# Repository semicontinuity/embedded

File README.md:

Embedded projects.
================================================================================

Projects for AVR microcontrollers.
--------------------------------------------------------------------------------
- [Primitive alarm](../../tree/master/target/alarm-a)
- [Primitive terminal](../../tree/master/target/display)
- [Voltage relay](../../tree/master/target/voltage-relay)
- [Mood lamp - firmware under development](../../tree/master/target/mood-lamp)
- [Primitive motion sensor controller, that works in pair with primitive alarm](../../tree/master/target/motion-sensor-controller/firmware/main)
- [Servo controller - unfinished, no firmware yet](../../tree/master/target/motor-controller/hardware)
- [LED dimmer, controlled via CAN bus](../../tree/master/target/plc-3u-a/firmware/network-led-dimmer)
- [CAN bus router - firmware under development](../../tree/master/target/plc-6u-a/firmware/can_router)
- [Roller shutter controller, controlled via CAN bus](../../tree/master/target/roller-shutter-controller/firmware/main)
- [Humidity meter](../../tree/master/target/plc-3u-b/firmware/humidity-meter)

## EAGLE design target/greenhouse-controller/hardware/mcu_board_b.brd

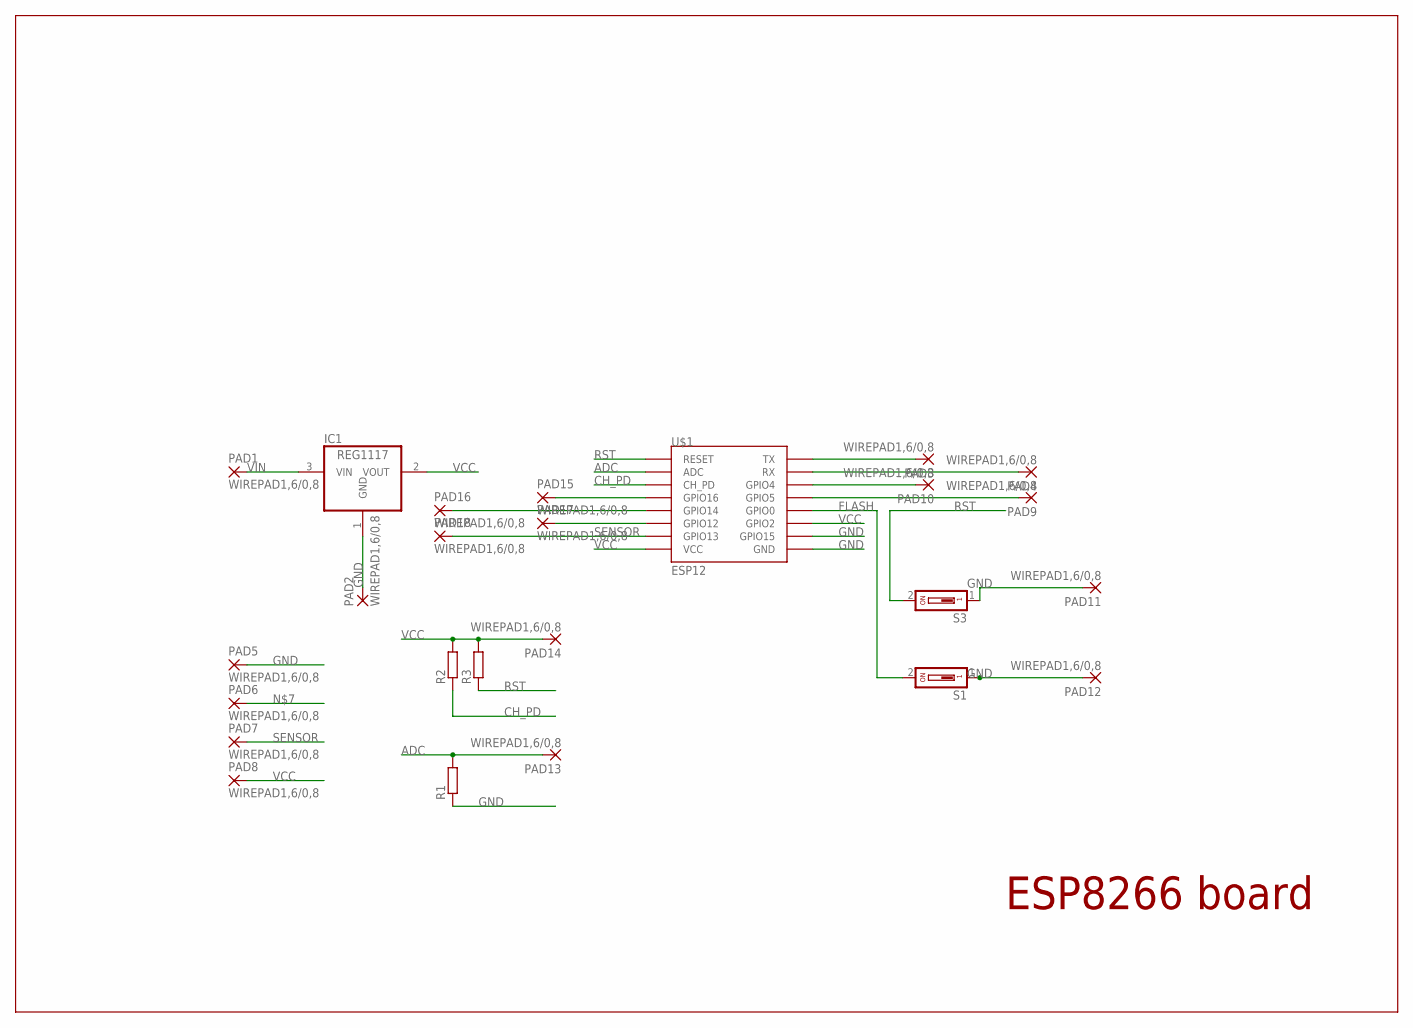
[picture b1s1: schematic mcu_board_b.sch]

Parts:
IC1: REG1117; SOT223
PAD1, PAD2, PAD3, PAD4, PAD5, PAD6, PAD7, PAD8, PAD9, PAD10, PAD11, PAD12, PAD13, PAD14, PAD15, PAD16, PAD17, PAD18: WIREPAD1,6/0,8; 1,6/0,8
R1, R2, R3: R-EU_M0805; M0805
S1, S3: DS01; DS-01
U$1: ESP12

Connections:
ADC: PAD13.1, R1.2, U$1.ADC
CH_PD: R2.1, U$1.CH_PD
FLASH: S1.2, U$1.GPIO0
GND: IC1.1 (GND), PAD2.1, PAD5.1, PAD11.1, PAD12.1, R1.1, S1.1, S3.1, U$1.GND, U$1.GPIO15
unnamed: PAD3.1, U$1.TX
unnamed: PAD4.1, U$1.RX
unnamed: PAD10.1, U$1.GPIO4
unnamed: PAD9.1, U$1.GPIO5
unnamed: PAD15.1, U$1.GPIO16
unnamed: PAD16.1, U$1.GPIO14
unnamed: PAD17.1, U$1.GPIO12
RST: R3.1, S3.2, U$1.RESET
SENSOR: PAD7.1, PAD18.1, U$1.GPIO13
VCC: IC1.2 (VOUT), PAD8.1, PAD14.1, R2.2, R3.2, U$1.GPIO2, U$1.VCC
VIN: IC1.3 (VIN), PAD1.1

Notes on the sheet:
ESP8266 board

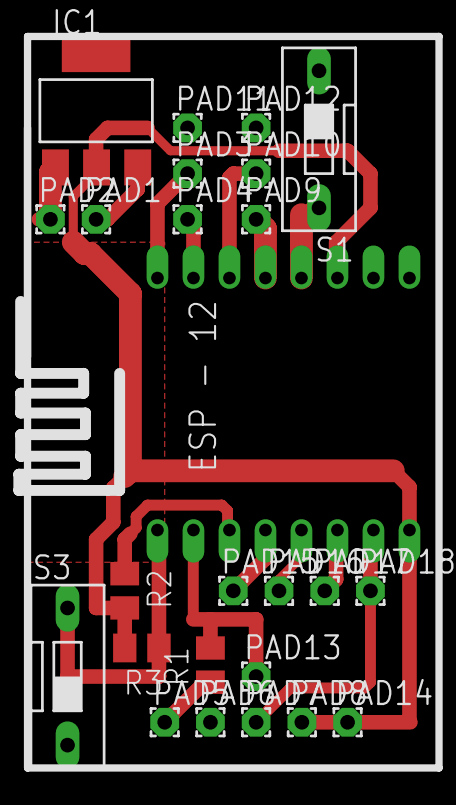
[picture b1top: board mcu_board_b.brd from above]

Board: 2 copper layers, 25 parts (0 on the bottom side), 15 nets.

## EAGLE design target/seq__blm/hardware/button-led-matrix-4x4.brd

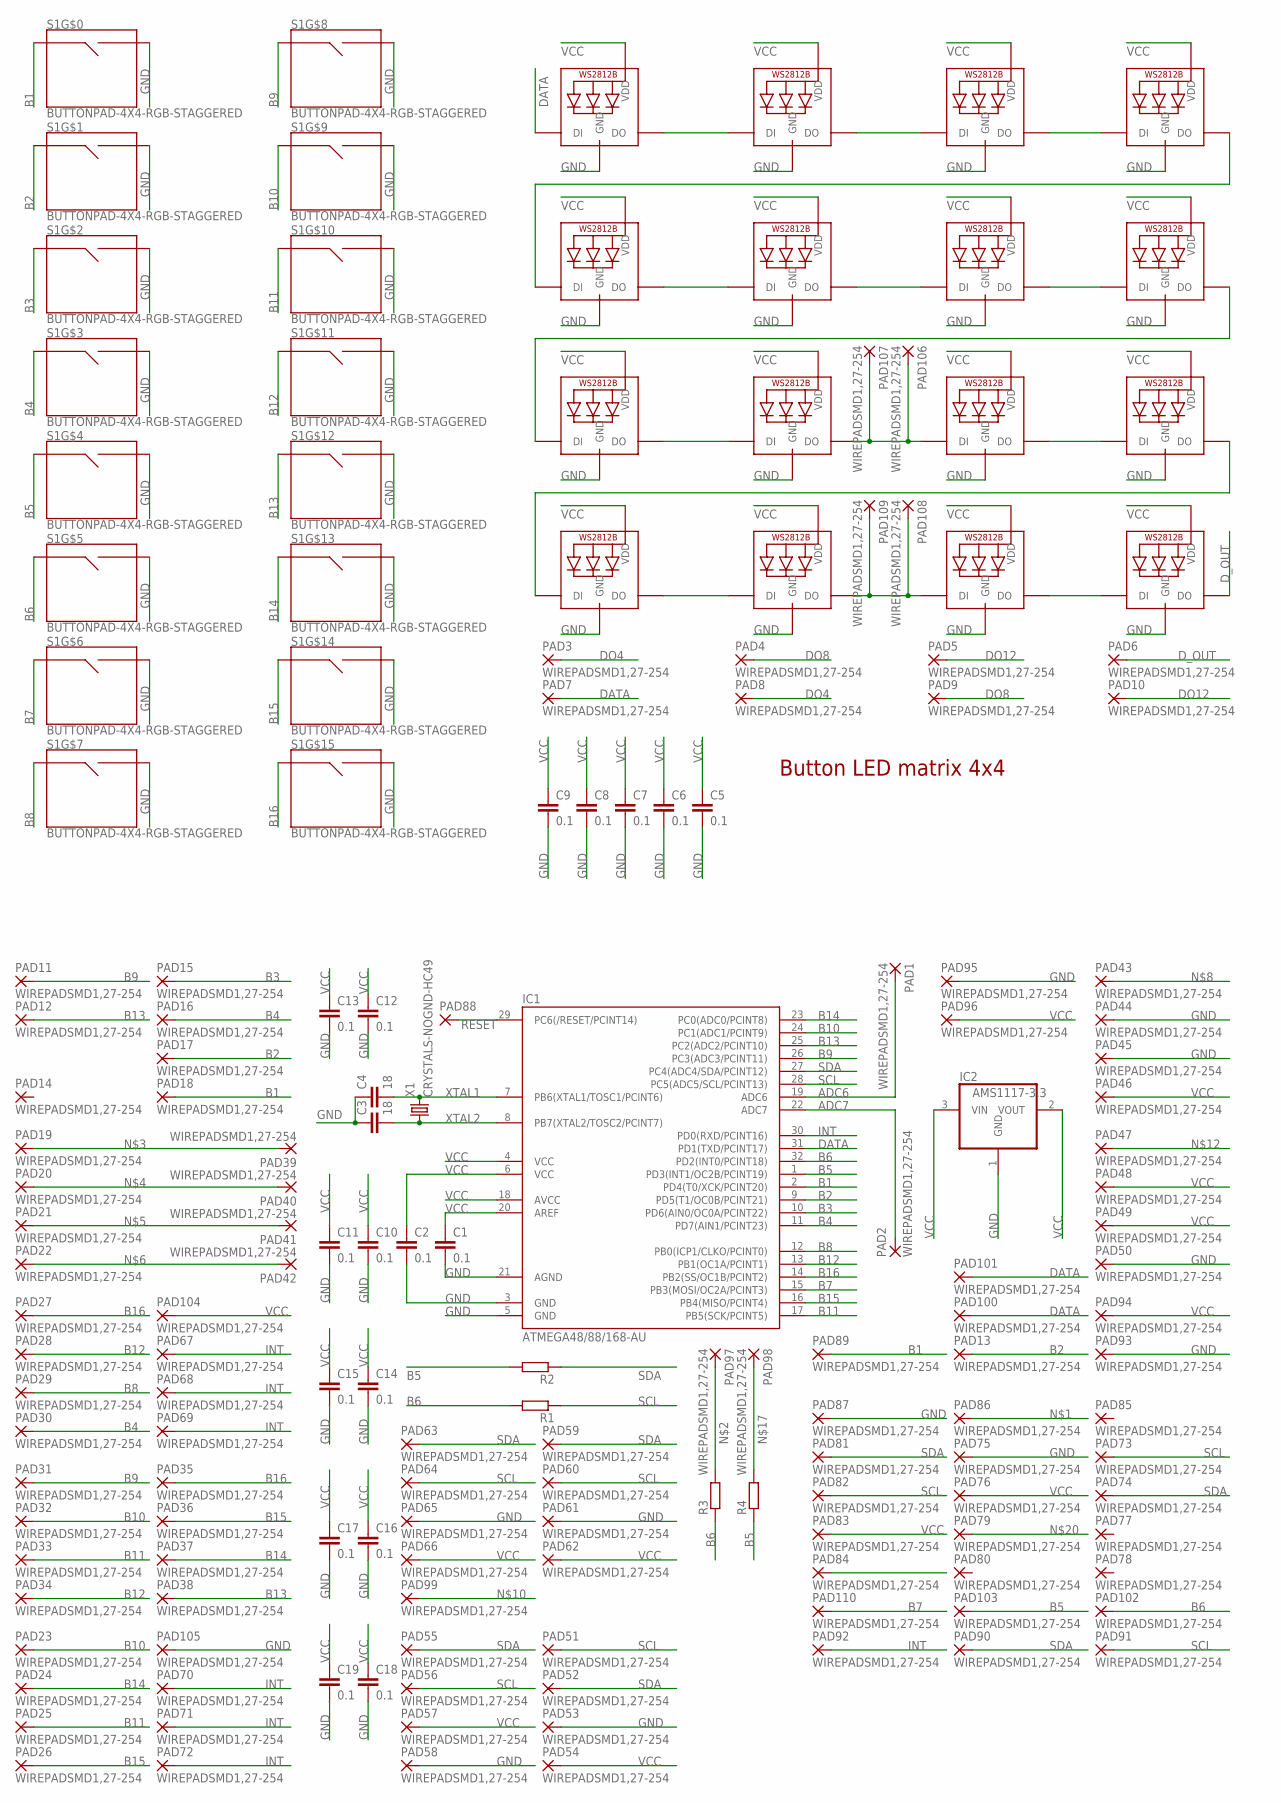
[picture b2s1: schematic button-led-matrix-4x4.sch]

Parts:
C1, C2, C5, C6, C7, C8, C9, C10, C11, C12, C13, C14, C15, C16, C17, C18, C19: 0.1; C0805
C3, C4: 18; C0805
IC1: ATMEGA48/88/168-AU; TQFP32-08
IC2: AMS1117-3.3; SOT223
LED1, LED2, LED3, LED4, LED5, LED6, LED7, LED8, LED9, LED10, LED11, LED12, LED13, LED14, LED15, LED16: WS2812B_5050N; WS2812B-NARROW
PAD1, PAD2, PAD3, PAD4, PAD5, PAD6, PAD7, PAD8, PAD9, PAD10, PAD11, PAD12, PAD13, PAD14, PAD15, PAD16, PAD17, PAD18, PAD19, PAD20, PAD21, PAD22, PAD23, PAD24, PAD25, PAD26, PAD27, PAD28, PAD29, PAD30, PAD31, PAD32, PAD33, PAD34, PAD35, PAD36, PAD37, PAD38, PAD39, PAD40, PAD41, PAD42, PAD43, PAD44, PAD45, PAD46, PAD47, PAD48, PAD49, PAD50, PAD51, PAD52, PAD53, PAD54, PAD55, PAD56, PAD57, PAD58, PAD59, PAD60, PAD61, PAD62, PAD63, PAD64, PAD65, PAD66, PAD67, PAD68, PAD69, PAD70, PAD71, PAD72, PAD73, PAD74, PAD75, PAD76, PAD77, PAD78, PAD79, PAD80, PAD81, PAD82, PAD83, PAD84, PAD85, PAD86, PAD87, PAD89, PAD90, PAD91, PAD92, PAD93, PAD94, PAD95, PAD96, PAD97, PAD98, PAD99, PAD100, PAD101, PAD102, PAD103, PAD104, PAD105, PAD106, PAD107, PAD108, PAD109, PAD110: WIREPADSMD1,27-254; SMD1,27-2,54
PAD88: 1,6/0,8
R1, R2: R-EU_R1206; R1206
R3, R4: R-EU_R0805; R0805
S1: BUTTONPAD-4X4-RGB-STAGGERED; BUTTONPAD-4X4-STAGGERED
X1: CRYSTALS-NOGND-HC49; HC49

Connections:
ADC6: IC1.19 (ADC6), PAD1.1
ADC7: IC1.22 (ADC7), PAD2.1
B1: IC1.2 (PD4(T0/XCK/PCINT20)), PAD18.1, PAD89.1, S1.SIG0 (SIG1)
B2: IC1.9 (PD5(T1/OC0B/PCINT21)), PAD13.1, PAD17.1, S1.SIG2 (SIG1)
B3: IC1.10 (PD6(AIN0/OC0A/PCINT22)), PAD15.1, S1.SIG4 (SIG1)
B4: IC1.11 (PD7(AIN1/PCINT23)), PAD16.1, PAD30.1, S1.SIG6 (SIG1)
B5: IC1.1 (PD3(INT1/OC2B/PCINT19)), PAD103.1, R2.2, R4.1, S1.SIG8 (SIG1)
B6: IC1.32 (PD2(INT0/PCINT18)), PAD102.1, R1.2, R3.1, S1.SIG10 (SIG1)
B7: IC1.15 (PB3(MOSI/OC2A/PCINT3)), PAD110.1, S1.SIG12 (SIG1)
B8: IC1.12 (PB0(ICP1/CLKO/PCINT0)), PAD29.1, S1.SIG14 (SIG1)
B9: IC1.26 (PC3(ADC3/PCINT11)), PAD11.1, PAD31.1, S1.SIG16 (SIG1)
B10: IC1.24 (PC1(ADC1/PCINT9)), PAD23.1, PAD32.1, S1.SIG18 (SIG1)
B11: IC1.17 (PB5(SCK/PCINT5)), PAD25.1, PAD33.1, S1.SIG20 (SIG1)
B12: IC1.13 (PB1(OC1A/PCINT1)), PAD28.1, PAD34.1, S1.SIG22 (SIG1)
B13: IC1.25 (PC2(ADC2/PCINT10)), PAD12.1, PAD38.1, S1.SIG24 (SIG1)
B14: IC1.23 (PC0(ADC0/PCINT8)), PAD24.1, PAD37.1, S1.SIG26 (SIG1)
B15: IC1.16 (PB4(MISO/PCINT4)), PAD26.1, PAD36.1, S1.SIG28 (SIG1)
B16: IC1.14 (PB2(SS/OC1B/PCINT2)), PAD27.1, PAD35.1, S1.SIG30 (SIG1)
DATA: IC1.31 (PD1(TXD/PCINT17)), LED1.4-DIN (DI), PAD7.1, PAD100.1, PAD101.1
DO1: LED1.2-DOUT (DO), LED2.4-DIN (DI)
DO2: LED2.2-DOUT (DO), LED3.4-DIN (DI)
DO3: LED3.2-DOUT (DO), LED4.4-DIN (DI)
DO4: LED4.2-DOUT (DO), LED5.4-DIN (DI), PAD3.1, PAD8.1
DO6: LED6.2-DOUT (DO), LED7.4-DIN (DI)
DO7: LED7.2-DOUT (DO), LED8.4-DIN (DI)
DO8: LED8.2-DOUT (DO), LED9.4-DIN (DI), PAD4.1, PAD9.1
DO9: LED9.2-DOUT (DO), LED10.4-DIN (DI)
DO10: LED10.2-DOUT (DO), LED11.4-DIN (DI), PAD106.1, PAD107.1
DO11: LED11.2-DOUT (DO), LED12.4-DIN (DI)
DO12: LED12.2-DOUT (DO), LED13.4-DIN (DI), PAD5.1, PAD10.1
DO13: LED13.2-DOUT (DO), LED14.4-DIN (DI)
DO14: LED14.2-DOUT (DO), LED15.4-DIN (DI), PAD108.1, PAD109.1
DO15: LED15.2-DOUT (DO), LED16.4-DIN (DI)
D_OUT: LED16.2-DOUT (DO), PAD6.1
FO5: LED5.2-DOUT (DO), LED6.4-DIN (DI)
GND: C1.2, C2.2, C3.1, C4.1, C5.2, C6.2, C7.2, C8.2, C9.2, C10.2, C11.2, C12.2, C13.2, C14.2, C15.2, C16.2, C17.2, C18.2, C19.2, IC1.3 (GND), IC1.5 (GND), IC1.21 (AGND), IC2.1 (GND), LED1.3-GND (GND), LED2.3-GND (GND), LED3.3-GND (GND), LED4.3-GND (GND), LED5.3-GND (GND), LED6.3-GND (GND), LED7.3-GND (GND), LED8.3-GND (GND), LED9.3-GND (GND), LED10.3-GND (GND), LED11.3-GND (GND), LED12.3-GND (GND), LED13.3-GND (GND), LED14.3-GND (GND), LED15.3-GND (GND), LED16.3-GND (GND), PAD44.1, PAD45.1, PAD50.1, PAD53.1, PAD58.1, PAD61.1, PAD65.1, PAD75.1, PAD87.1, PAD93.1, PAD95.1, PAD105.1, S1.SIG1 (SIG2), S1.SIG3 (SIG2), S1.SIG5 (SIG2), S1.SIG7 (SIG2), S1.SIG9 (SIG2), S1.SIG11 (SIG2), S1.SIG13 (SIG2), S1.SIG15 (SIG2), S1.SIG17 (SIG2), S1.SIG19 (SIG2), S1.SIG21 (SIG2), S1.SIG23 (SIG2), S1.SIG25 (SIG2), S1.SIG27 (SIG2), S1.SIG29 (SIG2), S1.SIG31 (SIG2)
INT: IC1.30 (PD0(RXD/PCINT16)), PAD67.1, PAD68.1, PAD69.1, PAD70.1, PAD71.1, PAD72.1, PAD92.1
unnamed: PAD97.1, R3.2
unnamed: PAD19.1, PAD39.1
unnamed: PAD20.1, PAD40.1
unnamed: PAD21.1, PAD41.1
unnamed: PAD22.1, PAD42.1
unnamed: PAD98.1, R4.2
RESET: IC1.29 (PC6(/RESET/PCINT14)), PAD88.1
SCL: IC1.28 (PC5(ADC5/SCL/PCINT13)), PAD51.1, PAD56.1, PAD60.1, PAD64.1, PAD73.1, PAD82.1, PAD91.1, R1.1
SDA: IC1.27 (PC4(ADC4/SDA/PCINT12)), PAD52.1, PAD55.1, PAD59.1, PAD63.1, PAD74.1, PAD81.1, PAD90.1, R2.1
VCC: C1.1, C2.1, C5.1, C6.1, C7.1, C8.1, C9.1, C10.1, C11.1, C12.1, C13.1, C14.1, C15.1, C16.1, C17.1, C18.1, C19.1, IC1.4 (VCC), IC1.6 (VCC), IC1.18 (AVCC), IC1.20 (AREF), IC2.2 (VOUT), IC2.3 (VIN), LED1.1-VDD (VDD), LED2.1-VDD (VDD), LED3.1-VDD (VDD), LED4.1-VDD (VDD), LED5.1-VDD (VDD), LED6.1-VDD (VDD), LED7.1-VDD (VDD), LED8.1-VDD (VDD), LED9.1-VDD (VDD), LED10.1-VDD (VDD), LED11.1-VDD (VDD), LED12.1-VDD (VDD), LED13.1-VDD (VDD), LED14.1-VDD (VDD), LED15.1-VDD (VDD), LED16.1-VDD (VDD), PAD46.1, PAD48.1, PAD49.1, PAD54.1, PAD57.1, PAD62.1, PAD66.1, PAD76.1, PAD83.1, PAD94.1, PAD96.1, PAD104.1
XTAL1: C4.2, IC1.7 (PB6(XTAL1/TOSC1/PCINT6)), X1.2
XTAL2: C3.2, IC1.8 (PB7(XTAL2/TOSC2/PCINT7)), X1.1

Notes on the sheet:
Button LED matrix 4x4

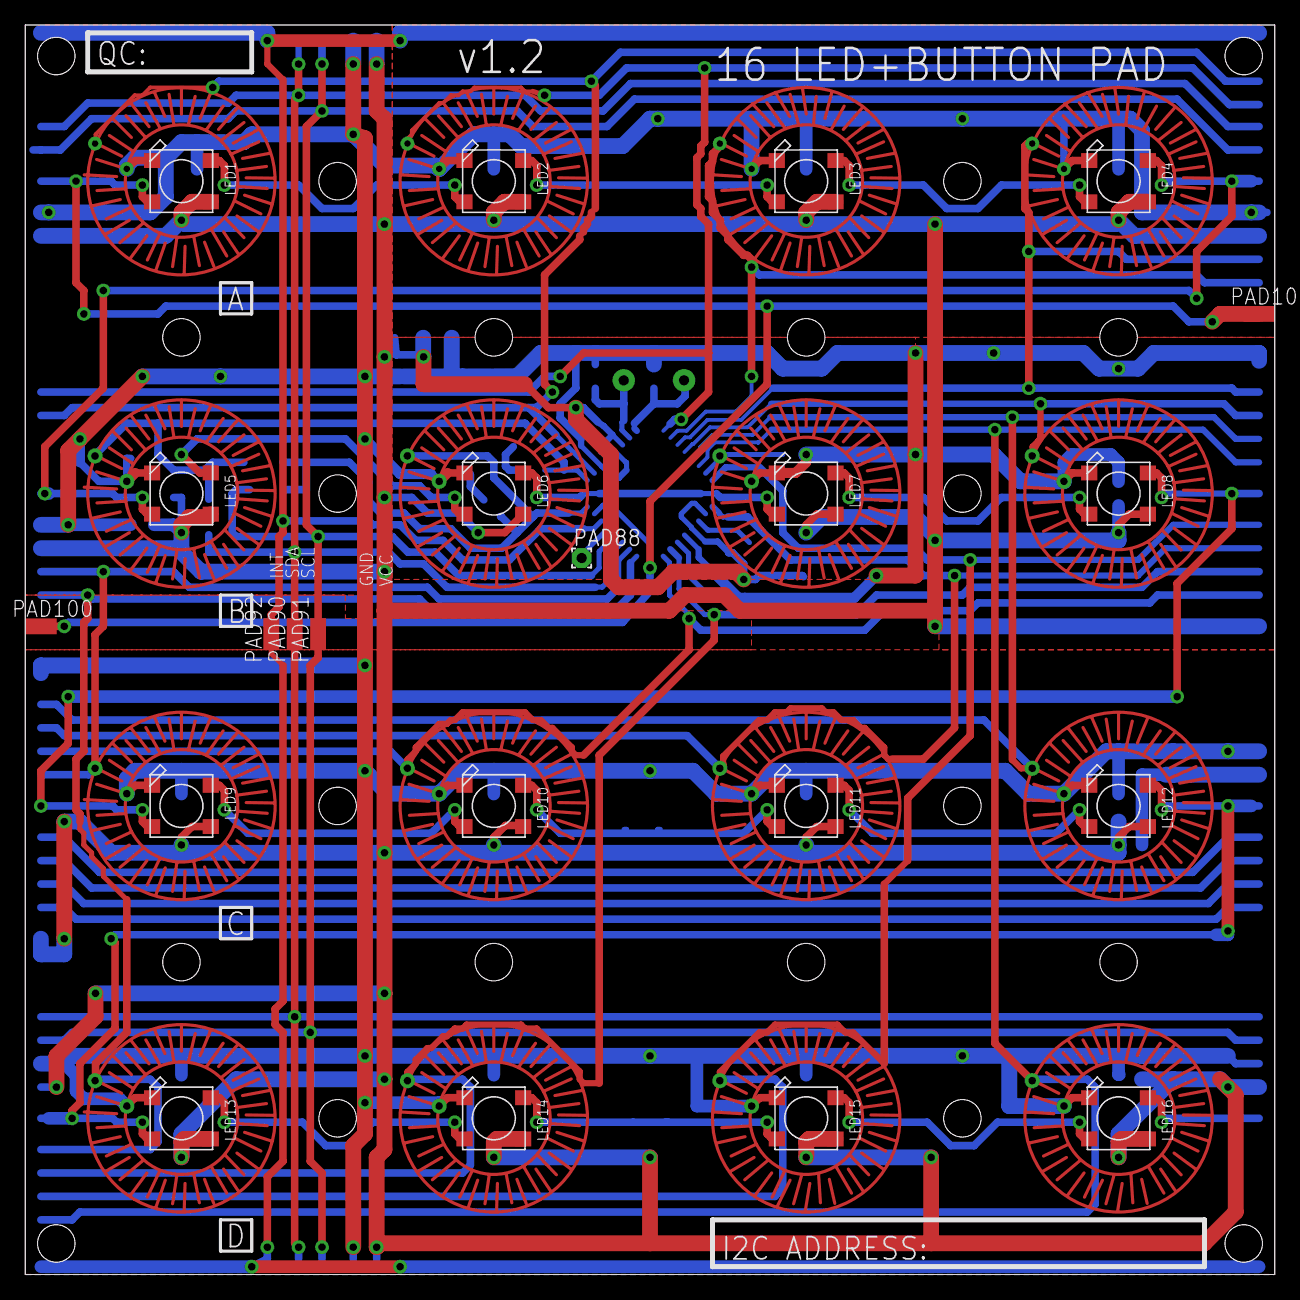
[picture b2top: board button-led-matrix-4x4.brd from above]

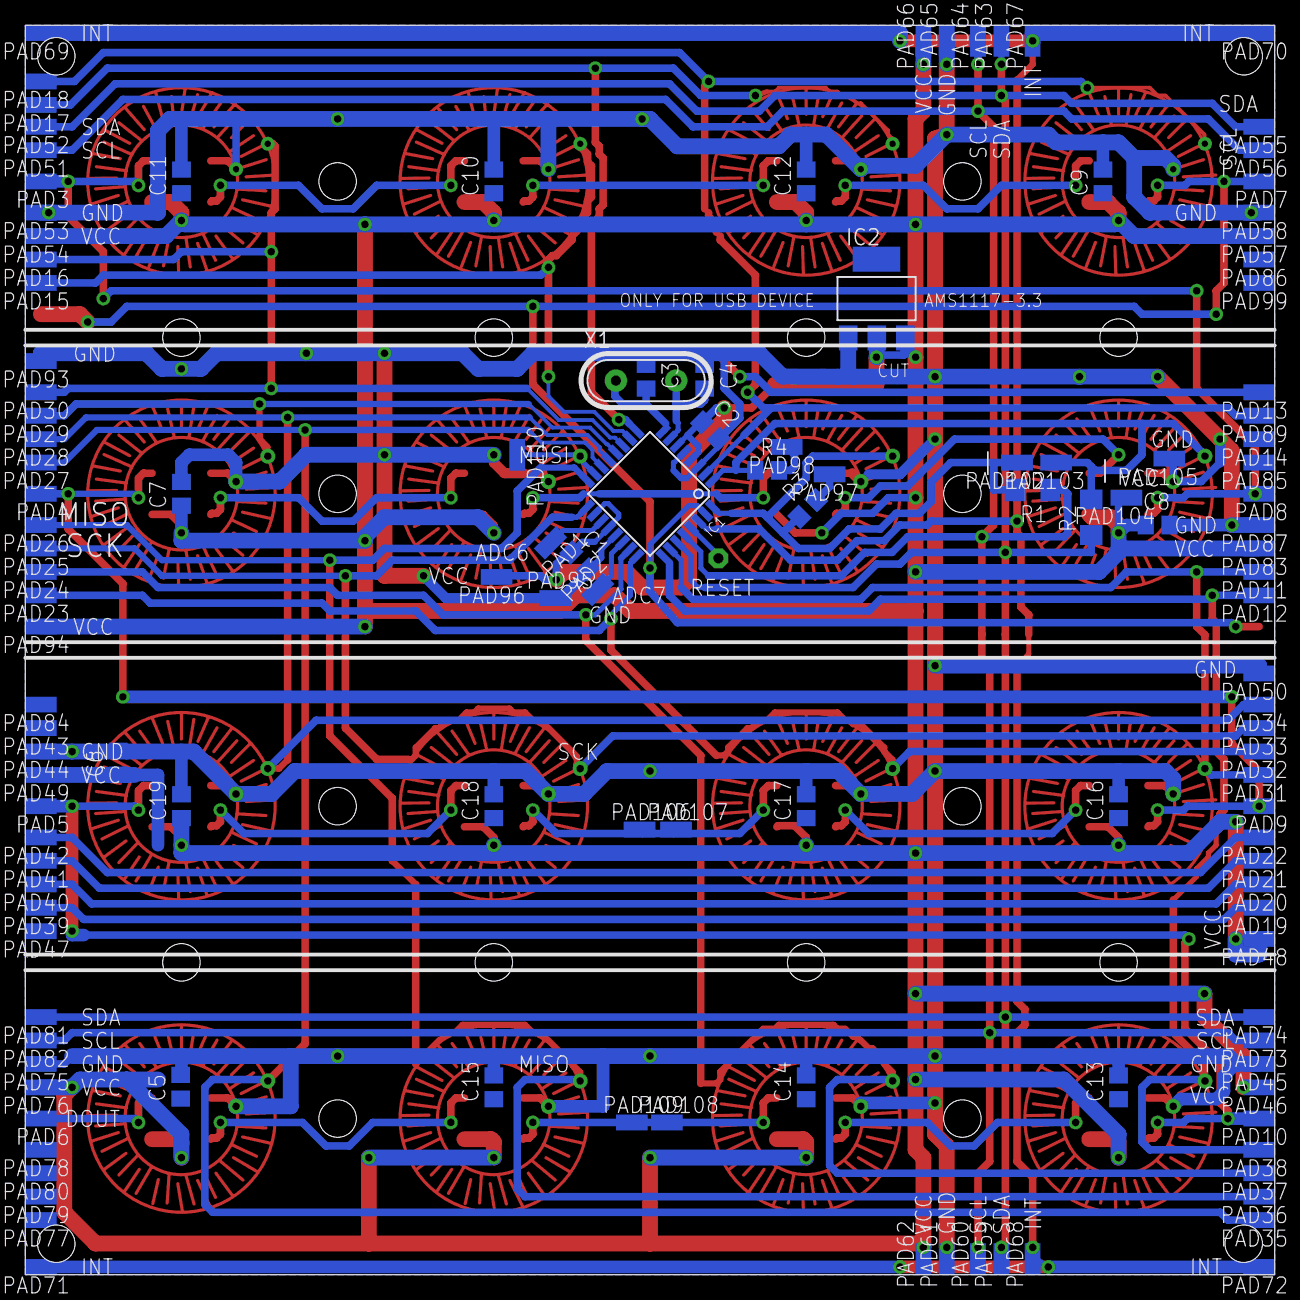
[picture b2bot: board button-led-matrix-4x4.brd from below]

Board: 2 copper layers, 100.0 x 100.0 mm, 153 parts (130 on the bottom side), 49 nets.

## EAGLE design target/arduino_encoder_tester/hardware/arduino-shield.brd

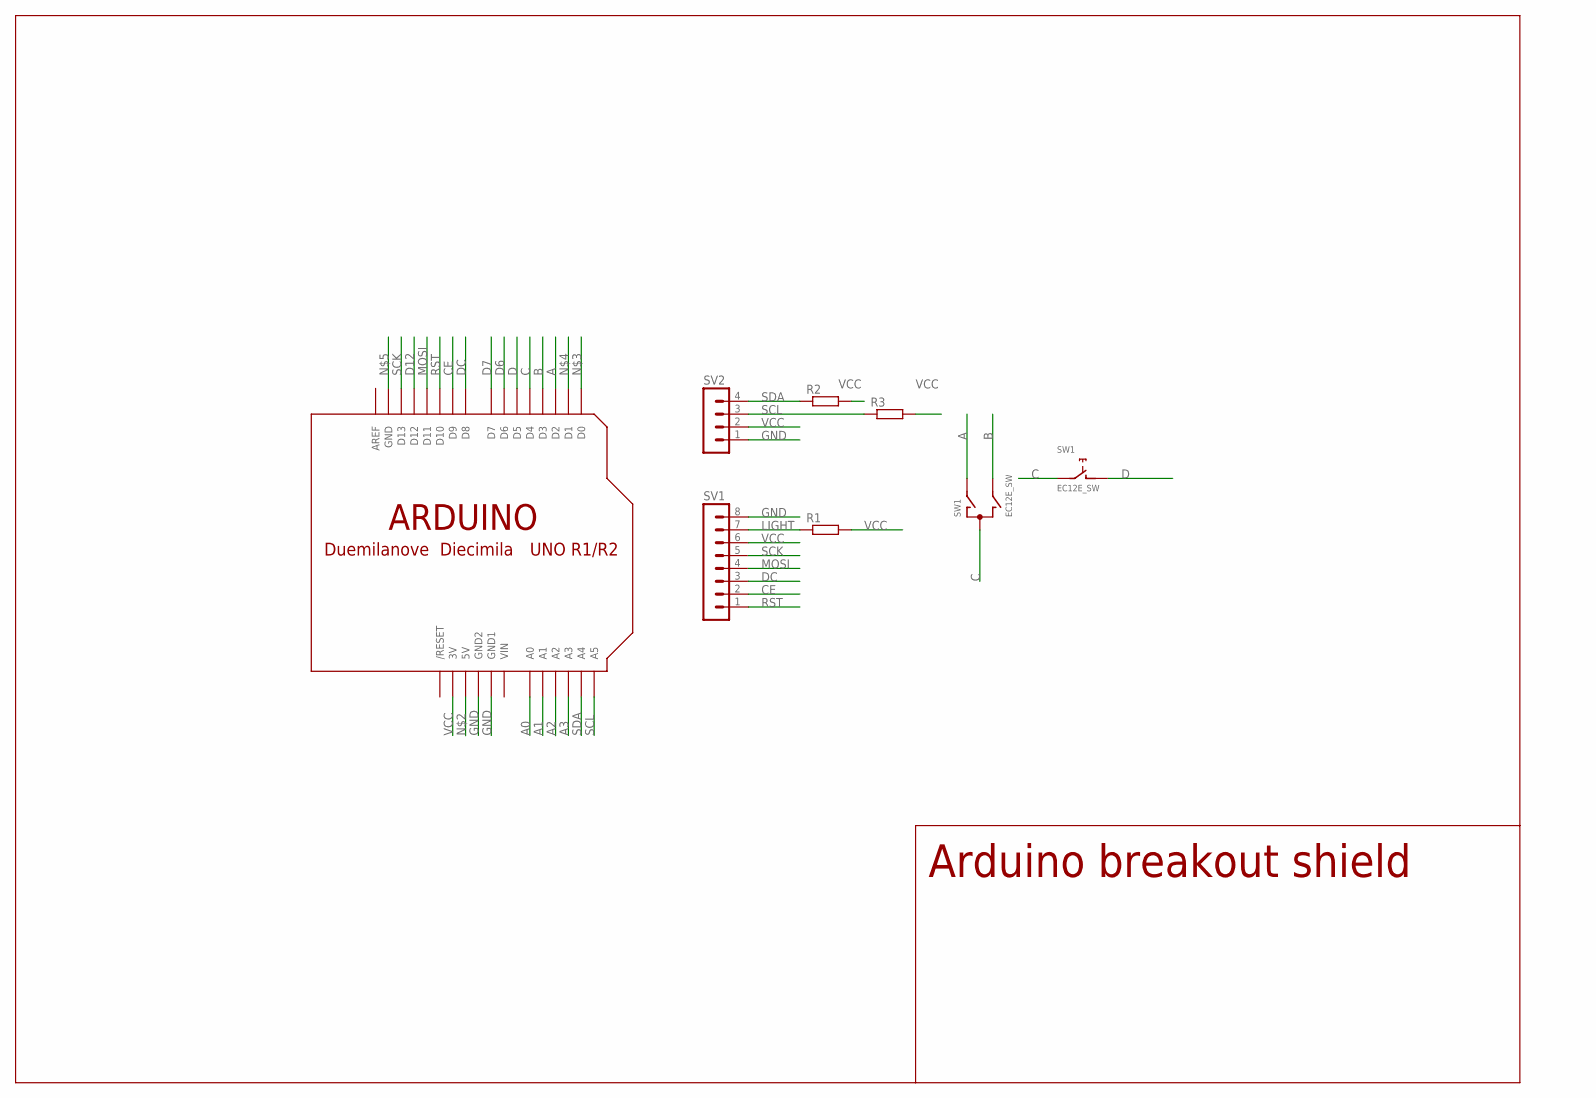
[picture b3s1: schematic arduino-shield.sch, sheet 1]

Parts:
R1, R2, R3: R-EU_R0805; R0805
SV1: MA08-1
SV2: MA04-1
SW1: EC12E_SW; ALPS_EC12E_SW
U$1: ARDUINO-NOHOLE

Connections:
A: SW1.A, U$1.D2
A0: U$1.A0
A1: U$1.A1
A2: U$1.A2
A3: U$1.A3
B: SW1.B, U$1.D3
C: SW1.C, SW1.E (2), U$1.D4
CE: SV1.2, U$1.D9
D: SW1.D (1), U$1.D5
D6: U$1.D6
D7: U$1.D7
D12: U$1.D12
DC: SV1.3, U$1.D8
GND: SV1.8, SV2.1, U$1.GND1, U$1.GND2
LIGHT: R1.1, SV1.7
MOSI: SV1.4, U$1.D11
RST: SV1.1, U$1.D10
SCK: SV1.5, U$1.D13
SCL: R3.1, SV2.3, U$1.A5
SDA: R2.1, SV2.4, U$1.A4
VCC: R1.2, R2.2, R3.2, SV1.6, SV2.2, U$1.3V
VIN: U$1.VIN

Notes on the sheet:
Arduino breakout shield

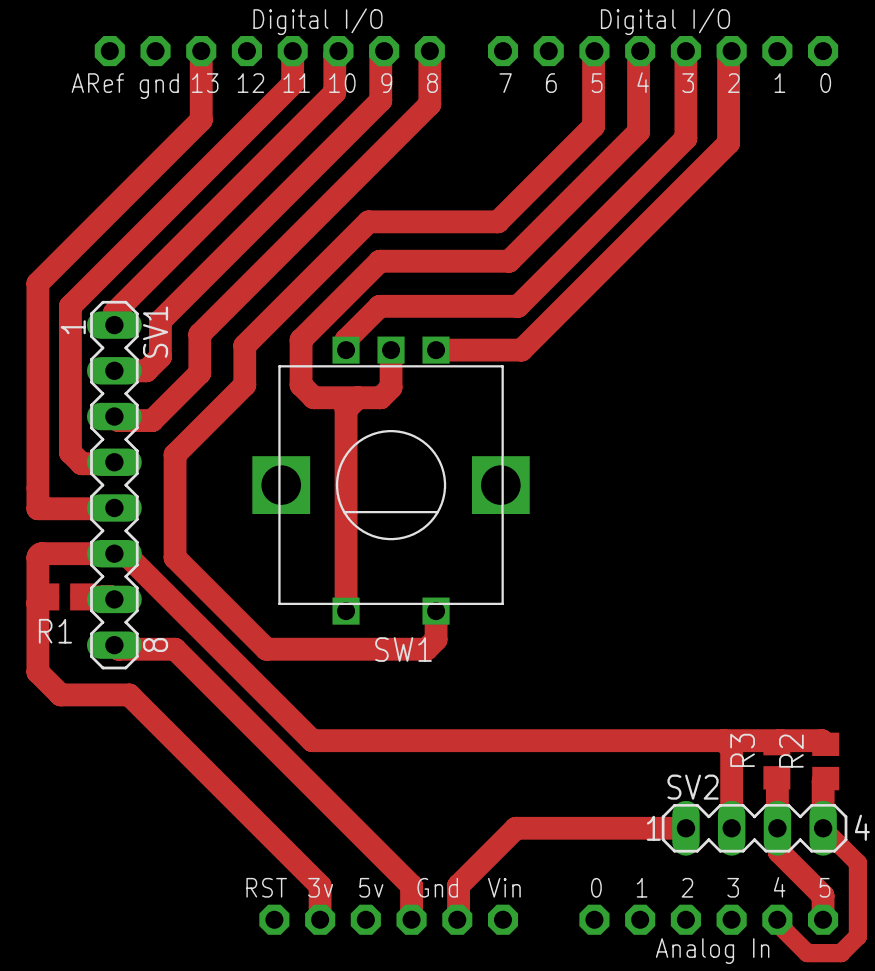
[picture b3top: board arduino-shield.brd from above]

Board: 2 copper layers, 7 parts (0 on the bottom side), 14 nets.

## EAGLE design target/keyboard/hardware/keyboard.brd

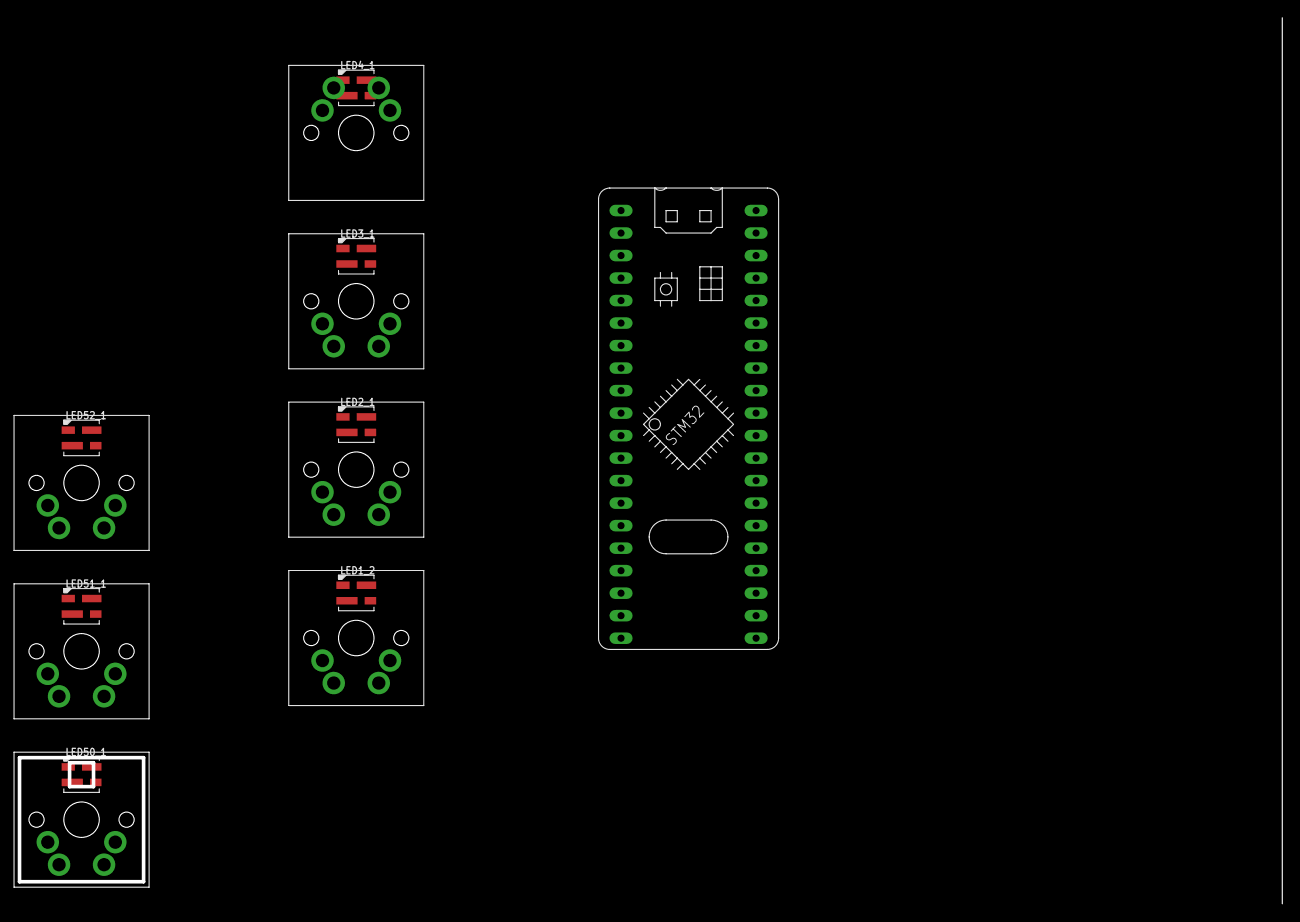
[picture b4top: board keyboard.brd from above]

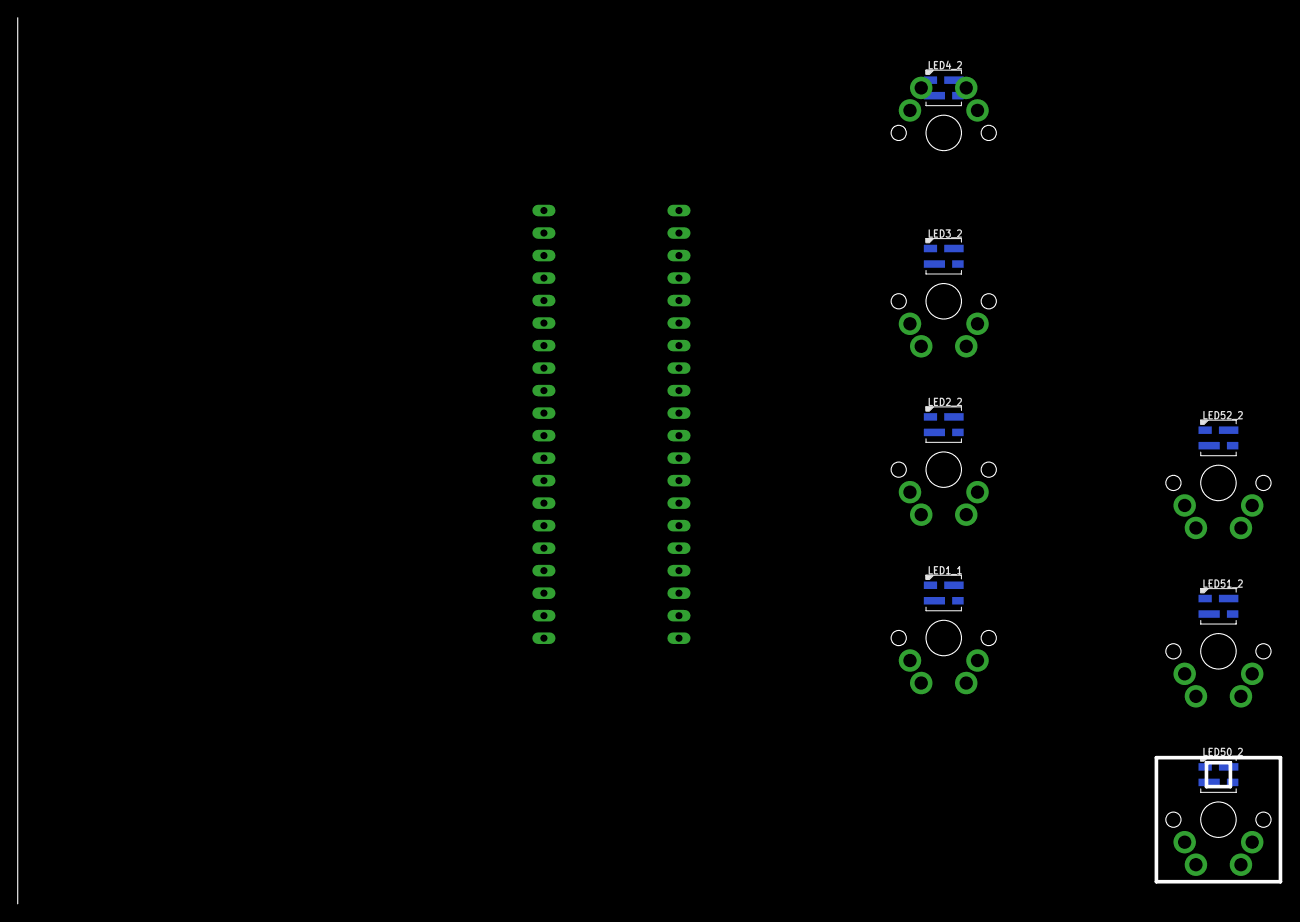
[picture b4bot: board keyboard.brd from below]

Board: 2 copper layers, 142.5 x 100.0 mm, 23 parts (7 on the bottom side), 2 nets, no tracks yet.

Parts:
LED1_1, LED1_2, LED2_1, LED2_2, LED3_1, LED3_2, LED4_1, LED4_2, LED50_1, LED50_2, LED51_1, LED51_2, LED52_1, LED52_2: LED3535
MCU: BLUE_PILL
SW1, SW2, SW3, SW4, SW50, SW51, SW52: CHERRY-MXSYMMETRIC; CHERRY-MX-SYMM
U$4: 3,0

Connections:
GND: LED1_1.2-GND, LED1_2.2-GND, LED2_1.2-GND, LED2_2.2-GND, LED3_1.2-GND, LED3_2.2-GND, LED4_1.2-GND, LED4_2.2-GND, LED50_1.2-GND, LED50_2.2-GND, LED51_1.2-GND, LED51_2.2-GND, LED52_1.2-GND, LED52_2.2-GND
VDD: LED1_1.4-VDD, LED1_2.4-VDD, LED2_1.4-VDD, LED2_2.4-VDD, LED3_1.4-VDD, LED3_2.4-VDD, LED4_1.4-VDD, LED4_2.4-VDD, LED50_1.4-VDD, LED50_2.4-VDD, LED51_1.4-VDD, LED51_2.4-VDD, LED52_1.4-VDD, LED52_2.4-VDD

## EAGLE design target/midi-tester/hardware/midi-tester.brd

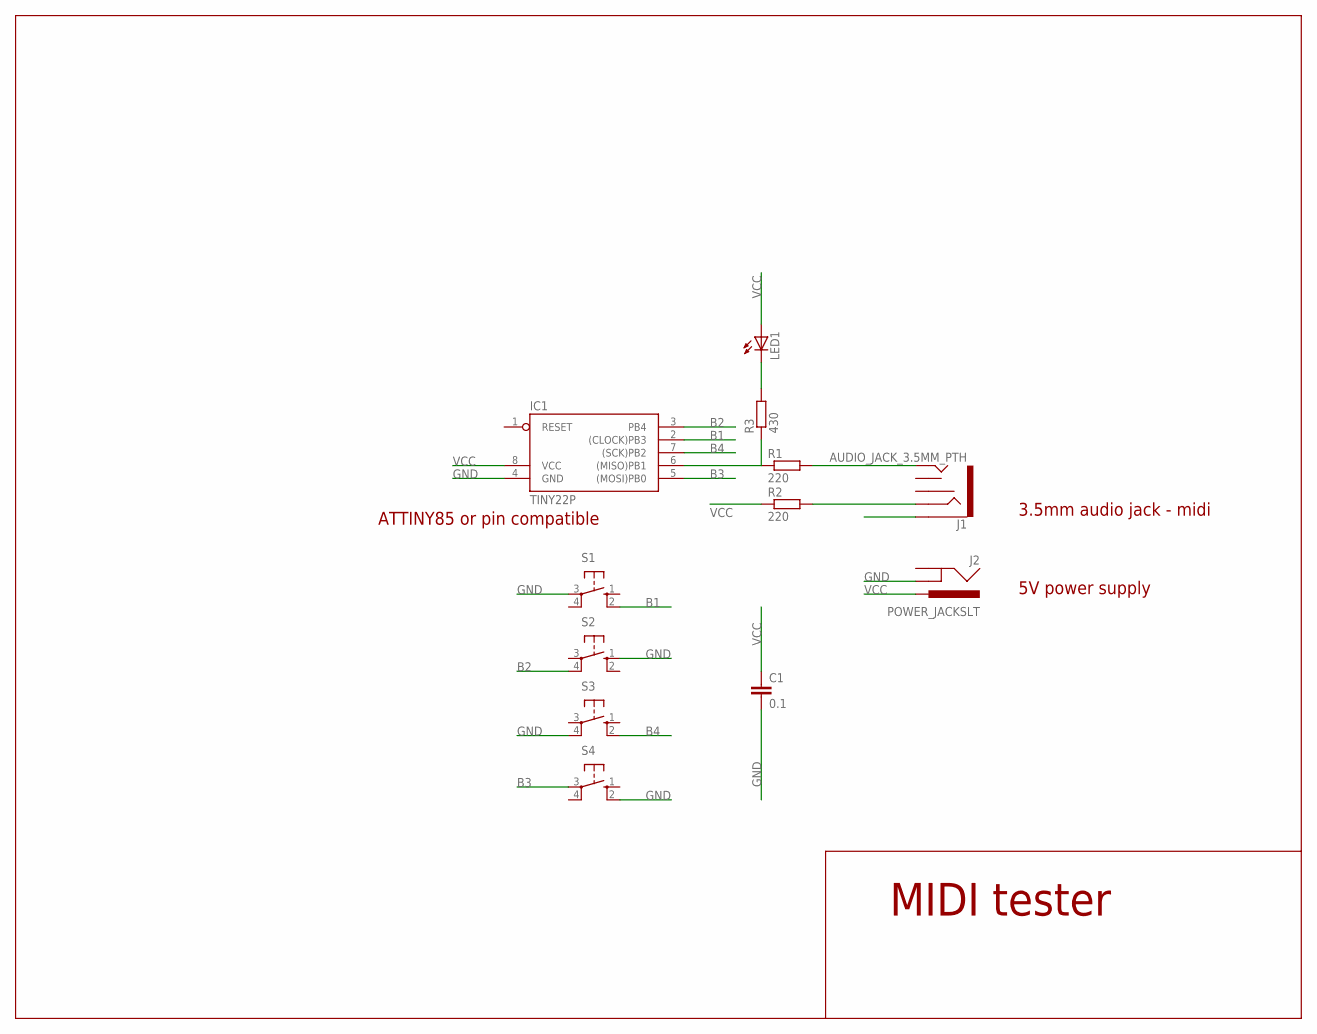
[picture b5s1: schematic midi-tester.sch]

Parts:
C1: 0.1; C0805
IC1: TINY22P; DIL08
J1: AUDIO_JACK_3.5MM_PTH; AUDIO-JACK
J2: POWER_JACKSLT; POWER_JACK_SLOT
LED1: LED5MM
R1, R2: 220; R0805
R3: 430; R0805
S1, S2, S3, S4: 10-XX; B3F-10XX

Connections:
B1: IC1.2 ((CLOCK)PB3), S1.2 (S1)
B2: IC1.3 (PB4), S2.4 (P1)
B3: IC1.5 ((MOSI)PB0), S4.3
B4: IC1.7 ((SCK)PB2), S3.2 (S1)
GND: C1.2, IC1.4 (GND), J1.SLEEVE, J2.GND@1 (GNDBREAK), S1.3, S2.1 (S), S3.4 (P1), S4.2 (S1)
unnamed: IC1.6 ((MISO)PB1), R1.1, R3.1
unnamed: J1.TIP, R1.2
unnamed: J1.RING, R2.2
unnamed: LED1.K (C), R3.2
VCC: C1.1, IC1.8 (VCC), J2.PWR, LED1.A, R2.1

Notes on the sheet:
MIDI tester
5V power supply
ATTINY85 or pin compatible
3.5mm audio jack - midi

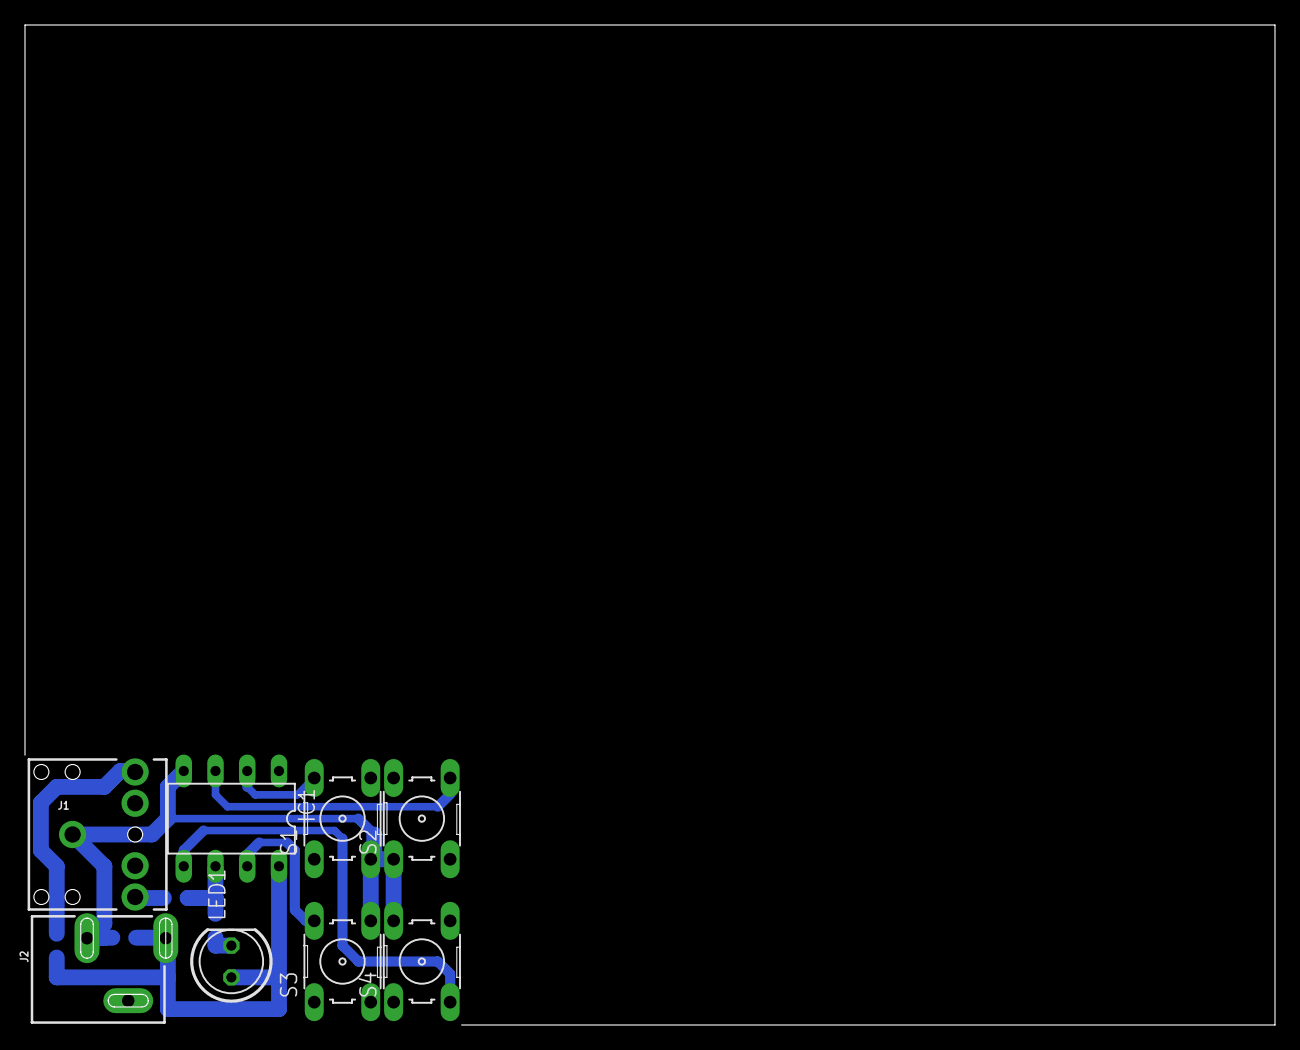
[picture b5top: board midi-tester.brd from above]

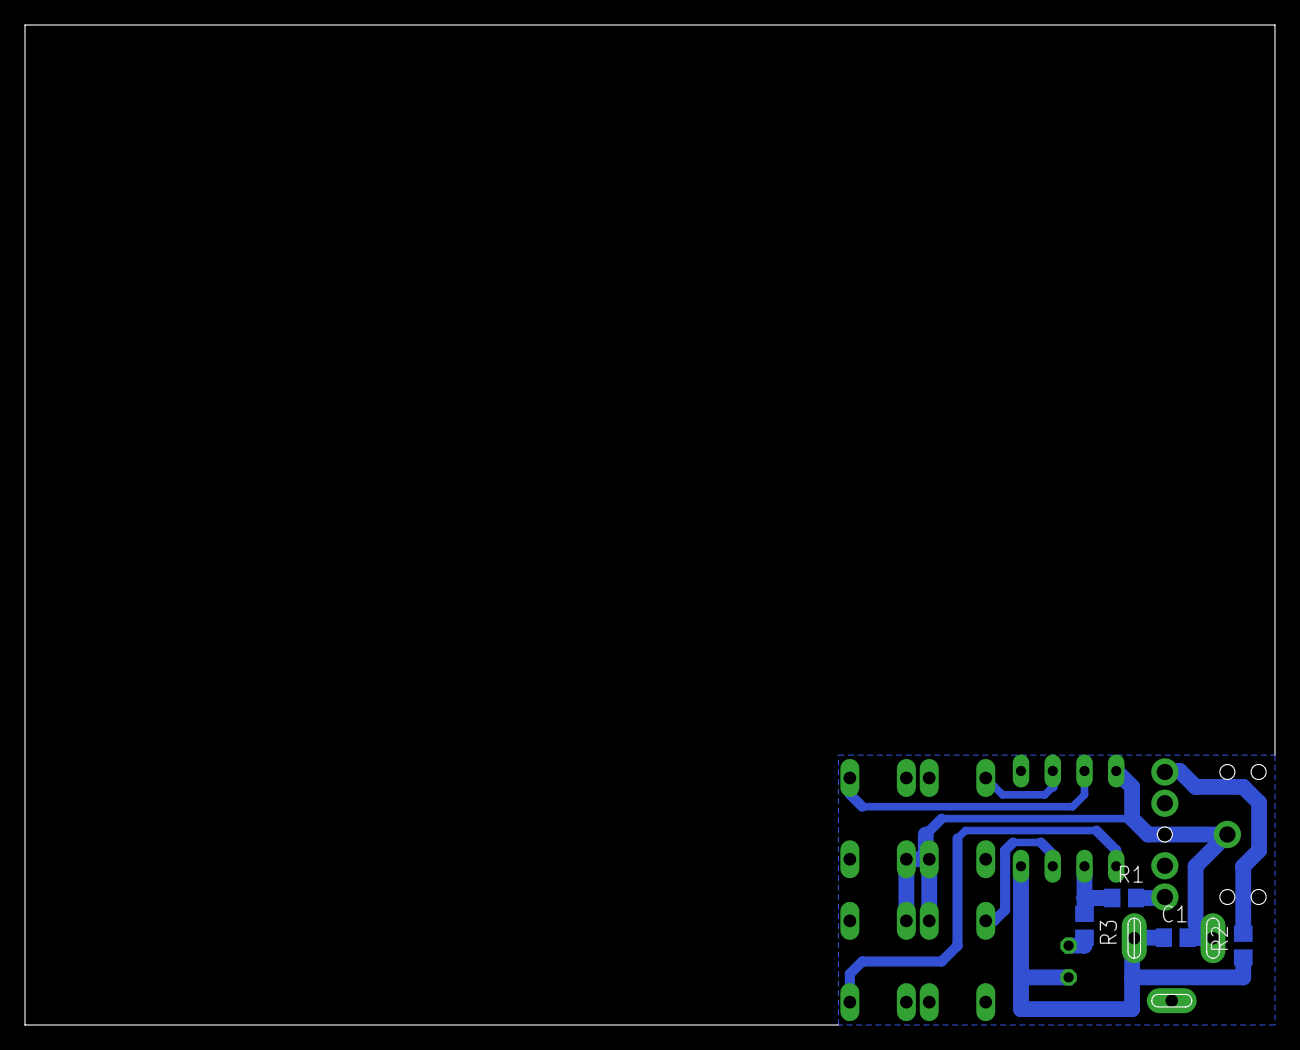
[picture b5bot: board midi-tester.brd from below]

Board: 2 copper layers, 100.0 x 80.0 mm, 12 parts (4 on the bottom side), 10 nets.

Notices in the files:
parts and their libraries:
SparkFun-Connectors: Licensing: Creative Commons ShareAlike 4.0 International - https://creativecommons.org/licenses/by-sa/4.0
